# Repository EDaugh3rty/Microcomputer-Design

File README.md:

# Microcomputer-Design
Microcomputer Design is a project where a single board computer is built. 
I selected and chose all of my different components after reading many datasheets to make the computer meet the requirements.
The PCB design came next so I had to take all of my different components and put them into Kicad to design a schematic and the board itself.
The operating system written in 68K Assembly code was made to make the computer read and write to memory, read and write to the registers, and to Load and Run an S-record.

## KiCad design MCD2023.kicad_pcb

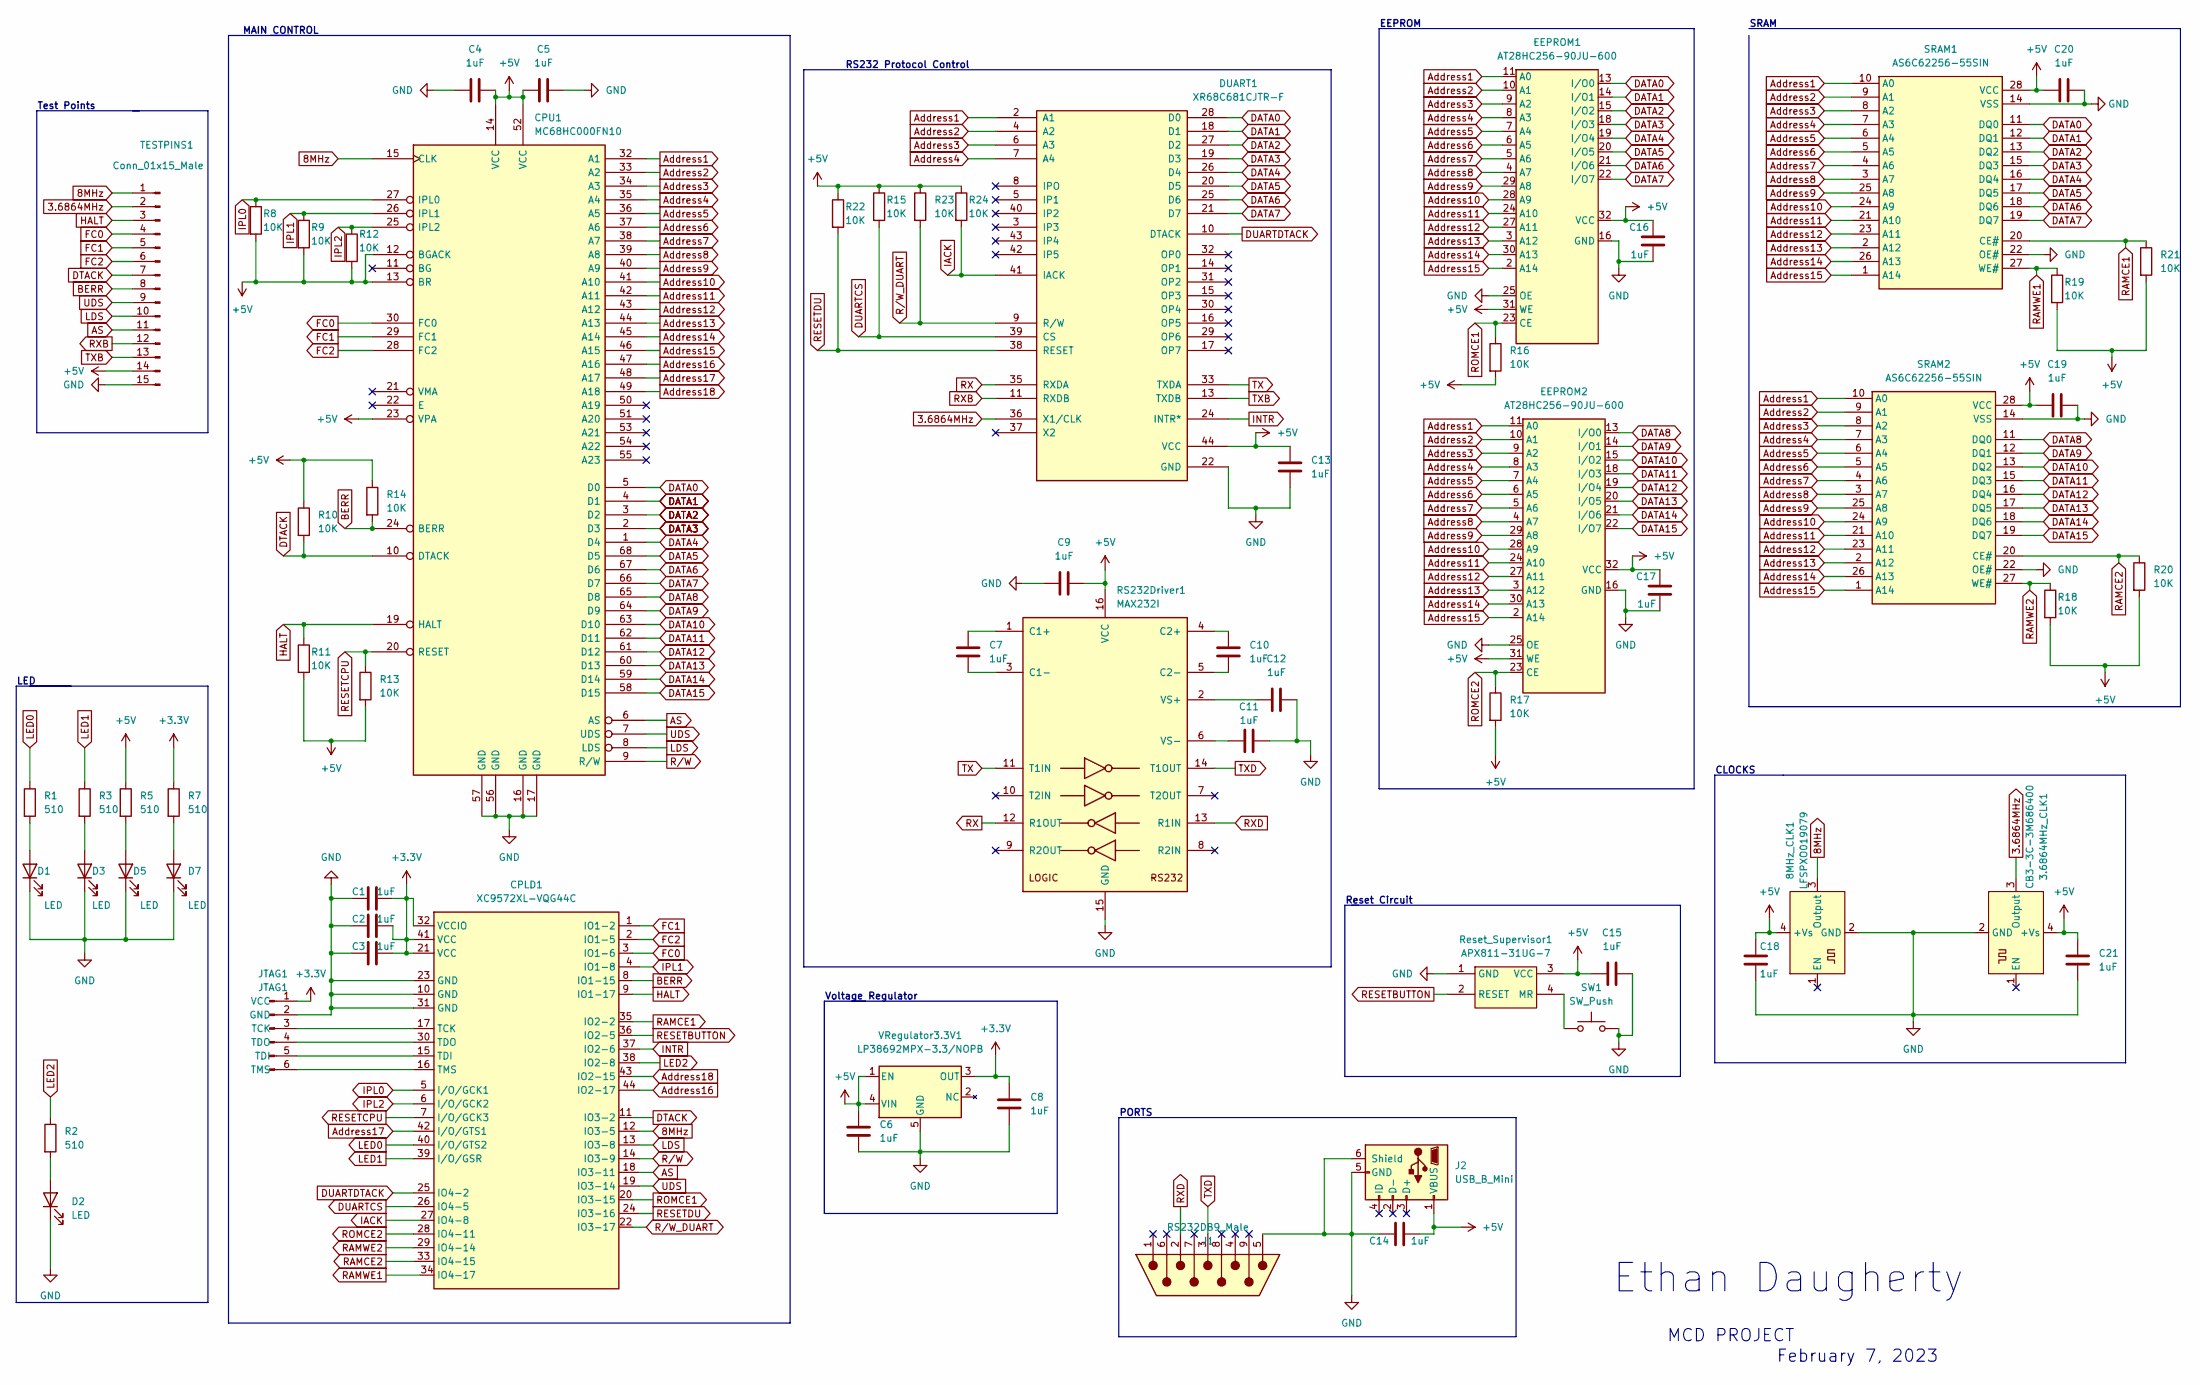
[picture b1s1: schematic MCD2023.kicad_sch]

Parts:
3.6864MHz_CLK1: CB3-3C-3M686400; Oscillator_SMD_IQD_IQXO70-4Pin_7.5x5.0mm
8MHz_CLK1: LFSPXO019079; Oscillator_SMD_IQD_IQXO70-4Pin_7.5x5.0mm_HandSoldering
C1, C2, C3, C4, C5, C6, C7, C8, C9, C10, C11, C12, C13, C14, C15, C16, C17, C18, C19, C20, C21: 1uF; C_0805_2012Metric_Pad1.18x1.45mm_HandSolder
CPLD1: XC9572XL-VQG44C; PLCC-44_THT-Socket
CPU1: MC68HC000FN10; PLCC-68_THT-Socket
D1, D2, D3, D5, D7: LED; LED_0805_2012Metric_Pad1.15x1.40mm_HandSolder
DUART1: XR68C681CJTR-F; PLCC-44_THT-Socket
EEPROM1, EEPROM2: AT28HC256-90JU-600; PLCC-32_THT-Socket
J1: RS232DB9_Male; DSUB-9_Male_Horizontal_P2.77x2.84mm_EdgePinOffset7.70mm_Hou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
J2: USB_B_Mini; USB_miniB_TH
JTAG1: JTAG1; JTAG
R1, R2, R3, R5, R7: 510; R_0805_2012Metric_Pad1.20x1.40mm_HandSolder
R8, R9, R10, R11, R12, R13, R14, R15, R16, R17, R18, R19, R20, R21, R22, R23, R24: 10K; R_0805_2012Metric_Pad1.20x1.40mm_HandSolder
RS232Driver1: MAX232I; SOIC-16
Reset_Supervisor1: APX811-31UG-7; SOT-143
SRAM1, SRAM2: AS6C62256-55SIN; SOP-28_V2
SW1: SW_Push; SW_SPST_B3S-1000
TESTPINS1: Conn_01x15_Male; MCD_TESTPOINTS
VRegulator3.3V1: LP38692MPX-3.3/NOPB; SOT-223-5

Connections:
3.6864MHz: 3.6864MHz_CLK1.3 (Output), DUART1.36 (X1/CLK), TESTPINS1.2
8MHz: 8MHz_CLK1.3 (Output), CPLD1.12 (IO3-5), CPU1.15 (CLK), TESTPINS1.1
+3V3: C1.2, C2.2, C3.1, C8.1, CPLD1.21 (VCC), CPLD1.32 (VCCIO), CPLD1.41 (VCC), JTAG1.1 (VCC), R7.1, VRegulator3.3V1.3 (OUT)
+5V: 3.6864MHz_CLK1.4 (+Vs), 8MHz_CLK1.4 (+Vs), C4.2, C5.1, C6.1, C9.1, C13.2, C14.2, C15.1, C16.1, C17.1, C18.1, C19.1, C20.1, C21.1, CPU1.12 (BGACK), CPU1.13 (BR), CPU1.14 (VCC), CPU1.23 (VPA), CPU1.52 (VCC), DUART1.44 (VCC), EEPROM1.31 (WE), EEPROM1.32 (VCC), EEPROM2.31 (WE), EEPROM2.32 (VCC), J2.1 (VBUS), R5.1, R8.2, R9.2, R10.1, R11.2, R12.2, R13.2, R14.1, R15.1, R16.2, R17.2, R18.2, R19.2, R20.2, R21.2, R22.1, R23.1, R24.1, RS232Driver1.16 (VCC), Reset_Supervisor1.3 (VCC), SRAM1.28 (VCC), SRAM2.28 (VCC), TESTPINS1.14, VRegulator3.3V1.1 (EN), VRegulator3.3V1.4 (VIN)
AS: CPLD1.18 (IO3-11), CPU1.6 (AS), TESTPINS1.11
Address1: CPU1.32 (A1), DUART1.2 (A1), EEPROM1.11 (A0), EEPROM2.11 (A0), SRAM1.10 (A0), SRAM2.10 (A0)
Address2: CPU1.33 (A2), DUART1.4 (A2), EEPROM1.10 (A1), EEPROM2.10 (A1), SRAM1.9 (A1), SRAM2.9 (A1)
Address3: CPU1.34 (A3), DUART1.6 (A3), EEPROM1.9 (A2), EEPROM2.9 (A2), SRAM1.8 (A2), SRAM2.8 (A2)
Address4: CPU1.35 (A4), DUART1.7 (A4), EEPROM1.8 (A3), EEPROM2.8 (A3), SRAM1.7 (A3), SRAM2.7 (A3)
Address5: CPU1.36 (A5), EEPROM1.7 (A4), EEPROM2.7 (A4), SRAM1.6 (A4), SRAM2.6 (A4)
Address6: CPU1.37 (A6), EEPROM1.6 (A5), EEPROM2.6 (A5), SRAM1.5 (A5), SRAM2.5 (A5)
Address7: CPU1.38 (A7), EEPROM1.5 (A6), EEPROM2.5 (A6), SRAM1.4 (A6), SRAM2.4 (A6)
Address8: CPU1.39 (A8), EEPROM1.4 (A7), EEPROM2.4 (A7), SRAM1.3 (A7), SRAM2.3 (A7)
Address9: CPU1.40 (A9), EEPROM1.29 (A8), EEPROM2.29 (A8), SRAM1.25 (A8), SRAM2.25 (A8)
Address10: CPU1.41 (A10), EEPROM1.28 (A9), EEPROM2.28 (A9), SRAM1.24 (A9), SRAM2.24 (A9)
Address11: CPU1.42 (A11), EEPROM1.24 (A10), EEPROM2.24 (A10), SRAM1.21 (A10), SRAM2.21 (A10)
Address12: CPU1.43 (A12), EEPROM1.27 (A11), EEPROM2.27 (A11), SRAM1.23 (A11), SRAM2.23 (A11)
Address13: CPU1.44 (A13), EEPROM1.3 (A12), EEPROM2.3 (A12), SRAM1.2 (A12), SRAM2.2 (A12)
Address14: CPU1.45 (A14), EEPROM1.30 (A13), EEPROM2.30 (A13), SRAM1.26 (A13), SRAM2.26 (A13)
Address15: CPU1.46 (A15), EEPROM1.2 (A14), EEPROM2.2 (A14), SRAM1.1 (A14), SRAM2.1 (A14)
Address16: CPLD1.44 (IO2-17), CPU1.47 (A16)
Address17: CPLD1.42 (I/O/GTS1), CPU1.48 (A17)
Address18: CPLD1.43 (IO2-15), CPU1.49 (A18)
BERR: CPLD1.8 (IO1-15), CPU1.24 (BERR), R14.2, TESTPINS1.8
DATA0: CPU1.5 (D0), DUART1.28 (D0), EEPROM1.13 (I/O0), SRAM1.11 (DQ0)
DATA1: CPU1.4 (D1), DUART1.18 (D1), EEPROM1.14 (I/O1), SRAM1.12 (DQ1)
DATA2: CPU1.3 (D2), DUART1.27 (D2), EEPROM1.15 (I/O2), SRAM1.13 (DQ2)
DATA3: CPU1.2 (D3), DUART1.19 (D3), EEPROM1.18 (I/O3), SRAM1.15 (DQ3)
DATA4: CPU1.1 (D4), DUART1.26 (D4), EEPROM1.19 (I/O4), SRAM1.16 (DQ4)
DATA5: CPU1.68 (D5), DUART1.20 (D5), EEPROM1.20 (I/O5), SRAM1.17 (DQ5)
DATA6: CPU1.67 (D6), DUART1.25 (D6), EEPROM1.21 (I/O6), SRAM1.18 (DQ6)
DATA7: CPU1.66 (D7), DUART1.21 (D7), EEPROM1.22 (I/O7), SRAM1.19 (DQ7)
DATA8: CPU1.65 (D8), EEPROM2.13 (I/O0), SRAM2.11 (DQ0)
DATA9: CPU1.64 (D9), EEPROM2.14 (I/O1), SRAM2.12 (DQ1)
DATA10: CPU1.63 (D10), EEPROM2.15 (I/O2), SRAM2.13 (DQ2)
DATA11: CPU1.62 (D11), EEPROM2.18 (I/O3), SRAM2.15 (DQ3)
DATA12: CPU1.61 (D12), EEPROM2.19 (I/O4), SRAM2.16 (DQ4)
DATA13: CPU1.60 (D13), EEPROM2.20 (I/O5), SRAM2.17 (DQ5)
DATA14: CPU1.59 (D14), EEPROM2.21 (I/O6), SRAM2.18 (DQ6)
DATA15: CPU1.58 (D15), EEPROM2.22 (I/O7), SRAM2.19 (DQ7)
DTACK: CPLD1.11 (IO3-2), CPU1.10 (DTACK), R10.2, TESTPINS1.7
DUARTCS: CPLD1.26 (IO4-5), DUART1.39 (CS), R15.2
DUARTDTACK: CPLD1.25 (IO4-2), DUART1.10 (DTACK)
FC0: CPLD1.3 (IO1-6), CPU1.30 (FC0), TESTPINS1.4
FC1: CPLD1.1 (IO1-2), CPU1.29 (FC1), TESTPINS1.5
FC2: CPLD1.2 (IO1-5), CPU1.28 (FC2), TESTPINS1.6
GND: 3.6864MHz_CLK1.2 (GND), 8MHz_CLK1.2 (GND), C1.1, C2.1, C3.2, C4.1, C5.2, C6.2, C8.2, C9.2, C11.2, C12.2, C13.1, C14.1, C15.2, C16.2, C17.2, C18.2, C19.2, C20.2, C21.2, CPLD1.10 (GND), CPLD1.23 (GND), CPLD1.31 (GND), CPU1.16 (GND), CPU1.17 (GND), CPU1.56 (GND), CPU1.57 (GND), D1.1 (K), D2.1 (K), D3.1 (K), D5.1 (K), D7.1 (K), DUART1.22 (GND), EEPROM1.16 (GND), EEPROM1.25 (OE), EEPROM2.16 (GND), EEPROM2.25 (OE), J1.0, J1.5 (GND), J2.5 (GND), J2.6 (Shield), JTAG1.2 (GND), RS232Driver1.15 (GND), Reset_Supervisor1.1 (GND), SRAM1.14 (VSS), SRAM1.22 (OE#), SRAM2.14 (VSS), SRAM2.22 (OE#), SW1.2, TESTPINS1.15, VRegulator3.3V1.5 (GND)
HALT: CPLD1.9 (IO1-17), CPU1.19 (HALT), R11.1, TESTPINS1.3
IACK: CPLD1.27 (IO4-8), DUART1.41 (IACK), R24.2
INTR: CPLD1.37 (IO2-6), DUART1.24 (INTR*)
IPL0: CPLD1.5 (I/O/GCK1), CPU1.27 (IPL0), R8.1
IPL1: CPLD1.4 (IO1-8), CPU1.26 (IPL1), R9.1
IPL2: CPLD1.6 (I/O/GCK2), CPU1.25 (IPL2), R12.1
LDS: CPLD1.13 (IO3-8), CPU1.8 (LDS), TESTPINS1.10
LED0: CPLD1.40 (I/O/GTS2), R1.1
LED1: CPLD1.39 (I/O/GSR), R3.1
LED2: CPLD1.38 (IO2-8), R2.1
unnamed: C7.1, RS232Driver1.1 (C1+)
unnamed: C7.2, RS232Driver1.3 (C1-)
unnamed: C10.1, RS232Driver1.4 (C2+)
unnamed: C10.2, RS232Driver1.5 (C2-)
unnamed: C11.1, RS232Driver1.6 (VS-)
unnamed: C12.1, RS232Driver1.2 (VS+)
unnamed: CPLD1.15 (TDI), JTAG1.5 (TDI)
unnamed: CPLD1.16 (TMS), JTAG1.6 (TMS)
unnamed: CPLD1.17 (TCK), JTAG1.3 (TCK)
unnamed: CPLD1.30 (TDO), JTAG1.4 (TDO)
unnamed: D1.2 (A), R1.2
unnamed: D2.2 (A), R2.2
unnamed: D3.2 (A), R3.2
unnamed: D5.2 (A), R5.2
unnamed: D7.2 (A), R7.2
unnamed: Reset_Supervisor1.4 (MR), SW1.1
RAMCE1: CPLD1.35 (IO2-2), R21.1, SRAM1.20 (CE#)
RAMCE2: CPLD1.33 (IO4-15), R20.1, SRAM2.20 (CE#)
RAMWE1: CPLD1.34 (IO4-17), R19.1, SRAM1.27 (WE#)
RAMWE2: CPLD1.29 (IO4-14), R18.1, SRAM2.27 (WE#)
RESETBUTTON: CPLD1.36 (IO2-5), Reset_Supervisor1.2 (RESET)
RESETCPU: CPLD1.7 (I/O/GCK3), CPU1.20 (RESET), R13.1
RESETDU: CPLD1.24 (IO3-16), DUART1.38 (RESET), R22.2
ROMCE1: CPLD1.20 (IO3-15), EEPROM1.23 (CE), R16.1
ROMCE2: CPLD1.28 (IO4-11), EEPROM2.23 (CE), R17.1
RX: DUART1.35 (RXDA), RS232Driver1.12 (R1OUT)
RXB: DUART1.11 (RXDB), TESTPINS1.12
RXD: J1.2 (RXD), RS232Driver1.13 (R1IN)
R/W: CPLD1.14 (IO3-9), CPU1.9 (R/W)
R/W_DUART: CPLD1.22 (IO3-17), DUART1.9 (R/W), R23.2
TX: DUART1.33 (TXDA), RS232Driver1.11 (T1IN)
TXB: DUART1.13 (TXDB), TESTPINS1.13
TXD: J1.3 (TXD), RS232Driver1.14 (T1OUT)
UDS: CPLD1.19 (IO3-14), CPU1.7 (UDS), TESTPINS1.9

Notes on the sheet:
EEPROM
Ethan Daugherty
Reset Circuit
Voltage Regulator
PORTS
LED
MAIN CONTROL
RS232 Protocol Control
CLOCKS
February 7, 2023
Test Points
SRAM
MCD PROJECT

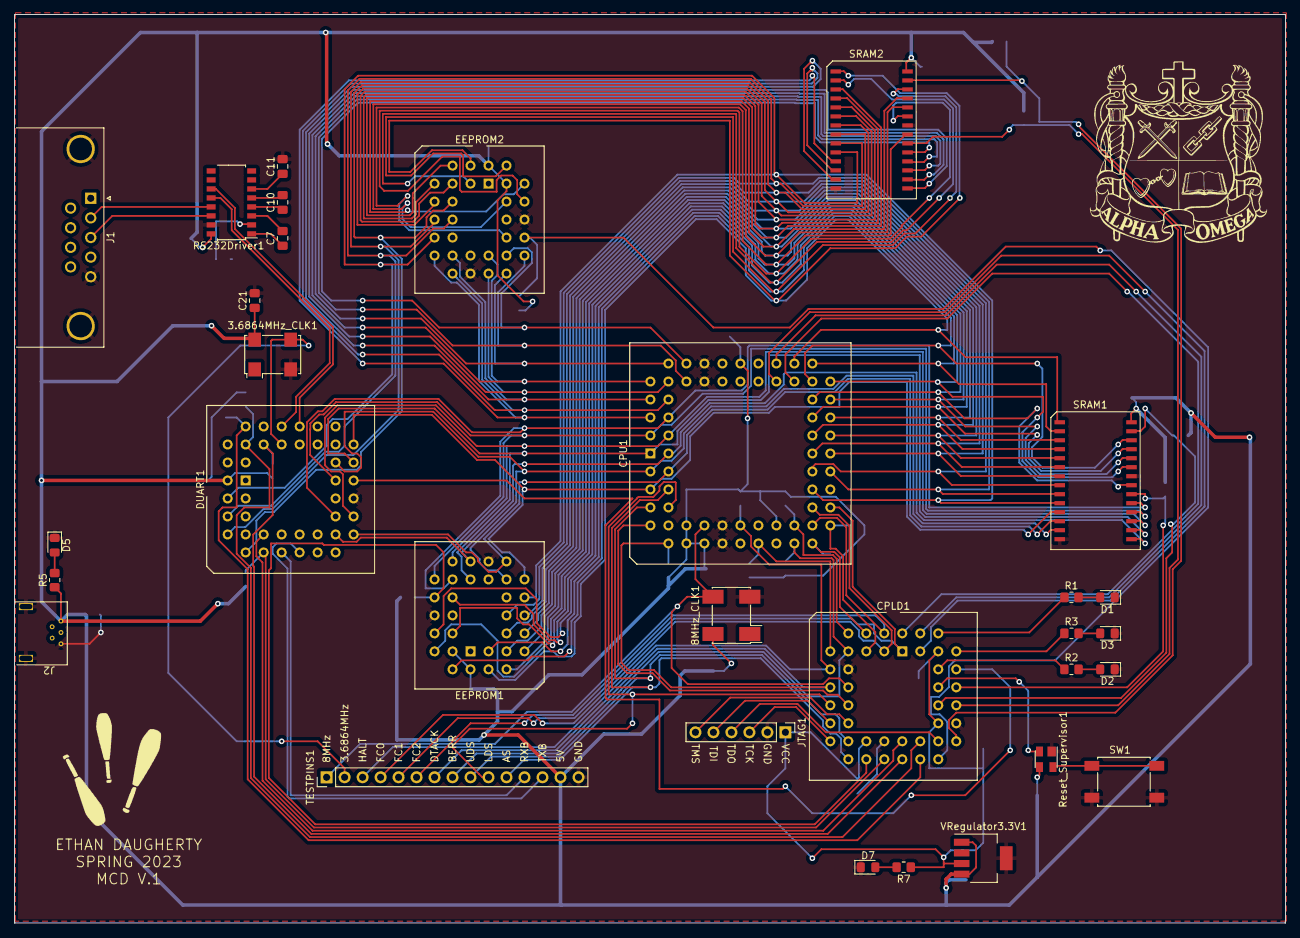
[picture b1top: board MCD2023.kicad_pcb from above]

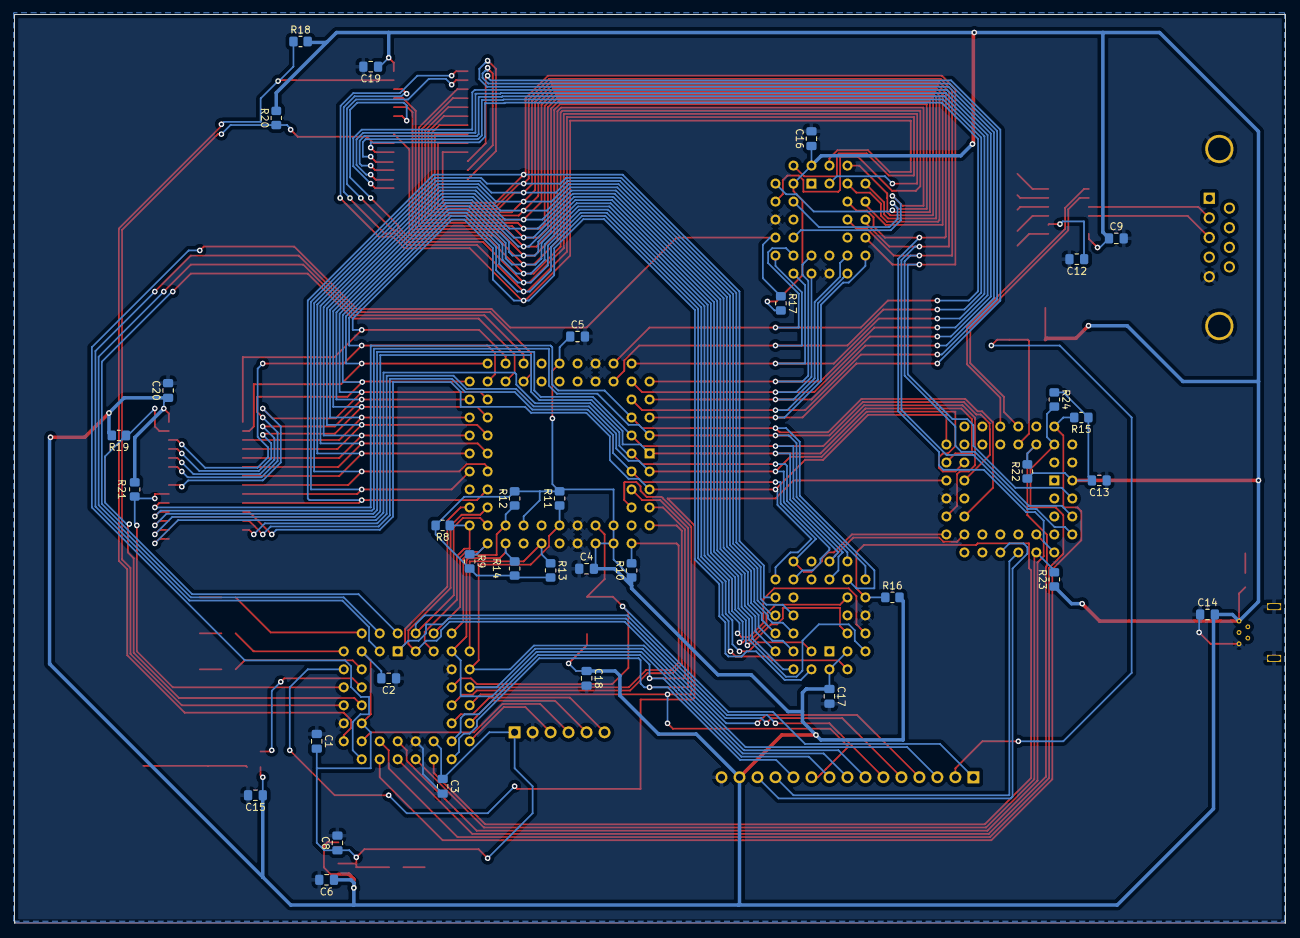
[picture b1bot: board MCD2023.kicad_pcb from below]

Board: 2 copper layers, 179.5 x 128.3 mm, 65 parts (34 on the bottom side), 91 nets.
